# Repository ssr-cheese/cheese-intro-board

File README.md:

# cheese\_intro\_board
This is a kicad project and PCB data for Micromouse with stepper motor developed by STM32F4.

# Layout
[CheeseUnua.pdf](./CheeseUnua.pdf)
# Requirement
STBee F4mini (https://strawberry-linux.com/catalog/items?code=32405)

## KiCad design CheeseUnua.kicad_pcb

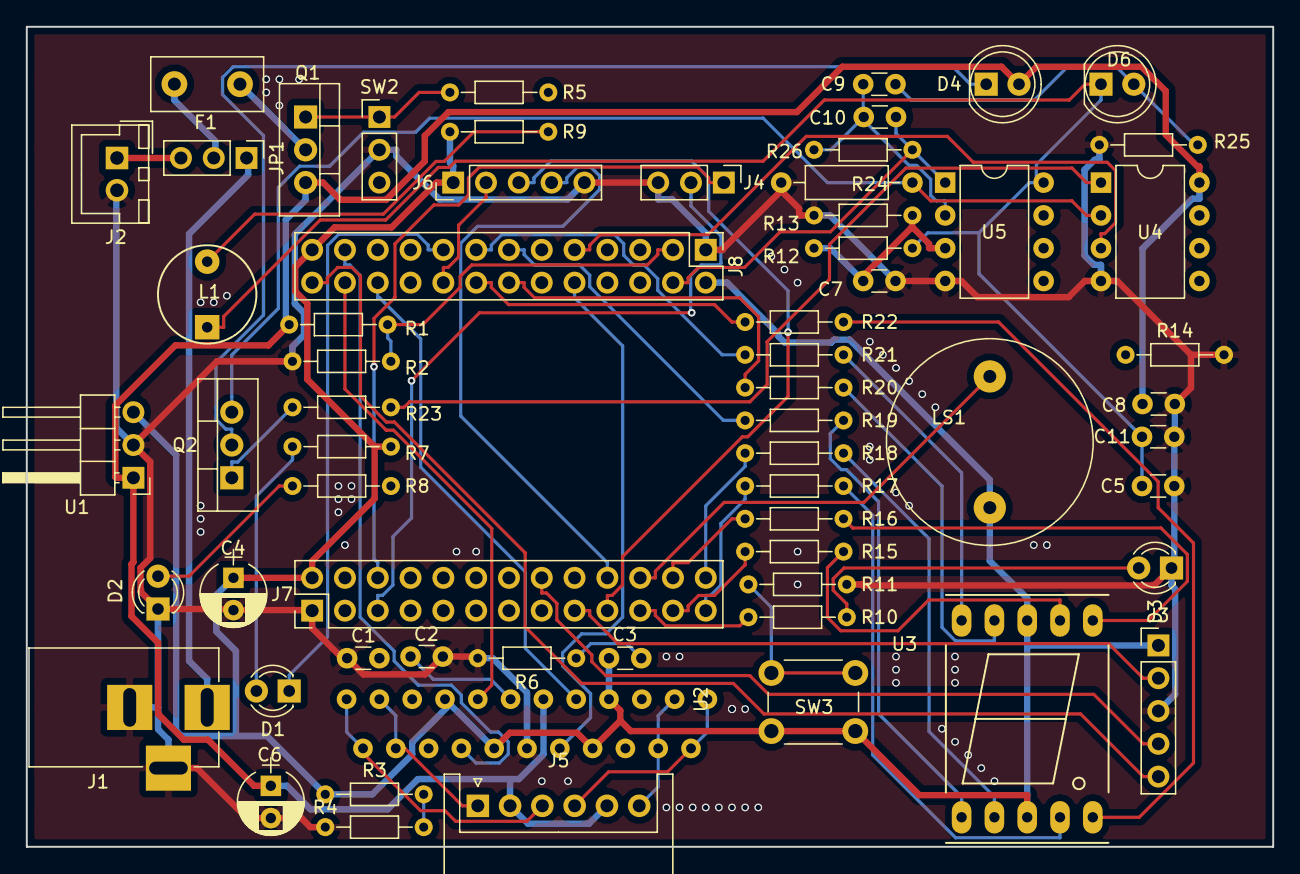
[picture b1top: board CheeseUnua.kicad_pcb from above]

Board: 2 copper layers, 96.5 x 63.5 mm, 63 parts (0 on the bottom side), 62 nets.

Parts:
C1: 1u; C_Disc_D3.0mm_W1.6mm_P2.50mm
C2, C3, C7, C8, C11: 0.1u; C_Disc_D3.0mm_W1.6mm_P2.50mm
C4: 10u; CP_Radial_D5.0mm_P2.50mm
C5: 10u; C_Disc_D3.0mm_W1.6mm_P2.50mm
C6: 100u; CP_Radial_D5.0mm_P2.50mm
C9: 0.01u; C_Disc_D3.0mm_W1.6mm_P2.50mm
C10: 22p; C_Disc_D3.0mm_W1.6mm_P2.50mm
D1, D2, D3: LED; LED_D3.0mm
D4: VSLY5850; LED_D5.0mm
D6: SFH213FA; LED_D5.0mm
F1: Polyfuse; Fuse_TE5_Littlefuse-395Series
J1: Jack-DC; BARREL_JACK
J2: Battery; JST_XH_B02B-XH-A_02x2.50mm_Straight
J3: Conn_01x05; Pin_Header_Straight_1x05_Pitch2.54mm
J4: Conn_01x03; Pin_Header_Straight_1x03_Pitch2.54mm
J5: Conn_01x06; JST_XH_S06B-XH-A_06x2.50mm_Angled
J6: AE-AQM0802; Pin_Header_Straight_1x05_Pitch2.54mm
J7: CN2; Pin_Header_Straight_2x13_Pitch2.54mm
J8: CN1; Pin_Header_Straight_2x13_Pitch2.54mm
JP1: Jumper_3_Bridged12; Pin_Header_Straight_1x03_Pitch2.54mm
L1: 100u; INDUCTOR_V
LS1: Speaker; BUZZER
Q1: 2SJ681; TO-220-3_Vertical
Q2: 2SK2796L; TO-220-3_Vertical
R1: 3.3k; R_Axial_DIN0204_L3.6mm_D1.6mm_P7.62mm_Horizontal
R2, R7, R8, R10, R12, R13, R15, R16, R17, R18, R19, R20, R21, R22: 1k; R_Axial_DIN0204_L3.6mm_D1.6mm_P7.62mm_Horizontal
R3, R6, R11, R14: 10k; R_Axial_DIN0204_L3.6mm_D1.6mm_P7.62mm_Horizontal
R4: 510; R_Axial_DIN0204_L3.6mm_D1.6mm_P7.62mm_Horizontal
R5, R25: 100k; R_Axial_DIN0204_L3.6mm_D1.6mm_P7.62mm_Horizontal
R9, R23: 10; R_Axial_DIN0204_L3.6mm_D1.6mm_P7.62mm_Horizontal
R24: 33; R_Axial_DIN0207_L6.3mm_D2.5mm_P10.16mm_Horizontal
R26: 220k; R_Axial_DIN0204_L3.6mm_D1.6mm_P7.62mm_Horizontal
SW2: SW_SPST; Pin_Header_Straight_1x03_Pitch2.54mm
SW3: SW_DPST_x2; SW_PUSH_6mm_h4.3mm
U1: R-78E3.3-0.5; Pin_Header_Angled_1x03_Pitch2.54mm
U2: SLA7073MPRT; SLA7073
U3: 7SEGMENT_CA; 7SegmentLED_LTS6760_LTS6780
U4: NJM2742D; DIP-8_W7.62mm
U5: NJU7072D; DIP-8_W7.62mm

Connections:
7SEG_A: J7.23, R15.2
7SEG_B: J7.24, R16.2
7SEG_C: J7.25, R17.2
7SEG_D: J7.26, R18.2
7SEG_E: J8.13, R19.2
7SEG_F: J8.14, R20.2
7SEG_G: J8.15, R21.2
7SEG_H: J8.16, R22.2
+3.3VA: C5.1, C11.1, D6.1, L1.1, R12.1, U5.8
+3V3: C3.1, C4.1, J3.1, J6.1, J7.2, J8.2, J8.25, LS1.1, R3.1, R7.1, R9.2, SW3.2, U1.3, U2.7, U2.8, U2.14, U2.17, U3.3, U3.8
+BATT: C6.1, C8.2, D4.2, J5.2, J5.5, Q1.3, R1.1, U1.1, U2.11, U4.8
/1.65V: C7.1, R12.2, R13.1, U5.3
BATT_MONITOR: J8.3, R1.2, R2.1
BUZZER: J7.22, LS1.2
GND: C1.2, C2.2, C4.2, C5.2, C6.2, C7.2, C8.1, C11.2, D2.1, D3.1, J1.2, J1.3, J2.2, J3.3, J4.3, J6.5, J7.1, J8.1, R2.2, R4.2, R6.2, R11.2, R13.2, R14.2, R24.2, R25.2, SW2.2, U1.2, U2.12, U4.4, U5.4
IR_LED: J8.9, U4.3
IR_SENSOR: C10.1, J8.4, R26.1, U5.1
LCD_RESET: J6.2, J8.18
LCD_SCL: J6.3, J7.19
LCD_SDA: J6.4, J7.20
LED: D1.1, J8.17
MOTOR_CLK: J8.10, U2.10
MOTOR_DIR: J8.23, U2.16
MOTOR_MODE: J8.22, U2.9
MOTOR_RESET: J8.24, U2.15
NRST: J3.5, J8.26
unnamed: C2.1, U2.13
unnamed: C3.2, R6.1
unnamed: C9.2, D6.2, R25.1
unnamed: C9.1, C10.2, R26.2, U5.2
unnamed: D1.2, R7.2
unnamed: D2.2, R8.2
unnamed: D3.2, R10.2
unnamed: D4.1, Q2.2
unnamed: F1.1, Q1.2
unnamed: F1.2, JP1.2
unnamed: J1.1, JP1.1
unnamed: J2.1, JP1.3
unnamed: J5.1, U2.20, U2.21
unnamed: J5.3, U2.22, U2.23
unnamed: J5.4, U2.1, U2.2
unnamed: J5.6, U2.3, U2.4
unnamed: L1.2, R9.1
unnamed: Q1.1, R5.2, SW2.1
unnamed: Q2.1, R23.1
unnamed: Q2.3, R24.1, U4.2
unnamed: R3.2, R4.1
unnamed: R11.1, SW3.1
unnamed: R15.1, U3.7
unnamed: R16.1, U3.6
unnamed: R17.1, U3.4
unnamed: R18.1, U3.2
unnamed: R19.1, U3.1
unnamed: R20.1, U3.9
unnamed: R21.1, U3.10
unnamed: R22.1, U3.5
unnamed: R23.2, U4.1
RX: J4.1, J7.6
SW: J7.21, R10.1
SWCLK: J3.2, J7.17
SWDIO: J3.4, J7.16
TX: J4.2, J7.5

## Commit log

2018-10-17 Step up to version 2
2018-10-17 Add pdf and README
2018-12-19 Add a pdf
2019-01-26 Add a board image
2019-01-26 Add a pdf data
2019-01-26 Fix layout
